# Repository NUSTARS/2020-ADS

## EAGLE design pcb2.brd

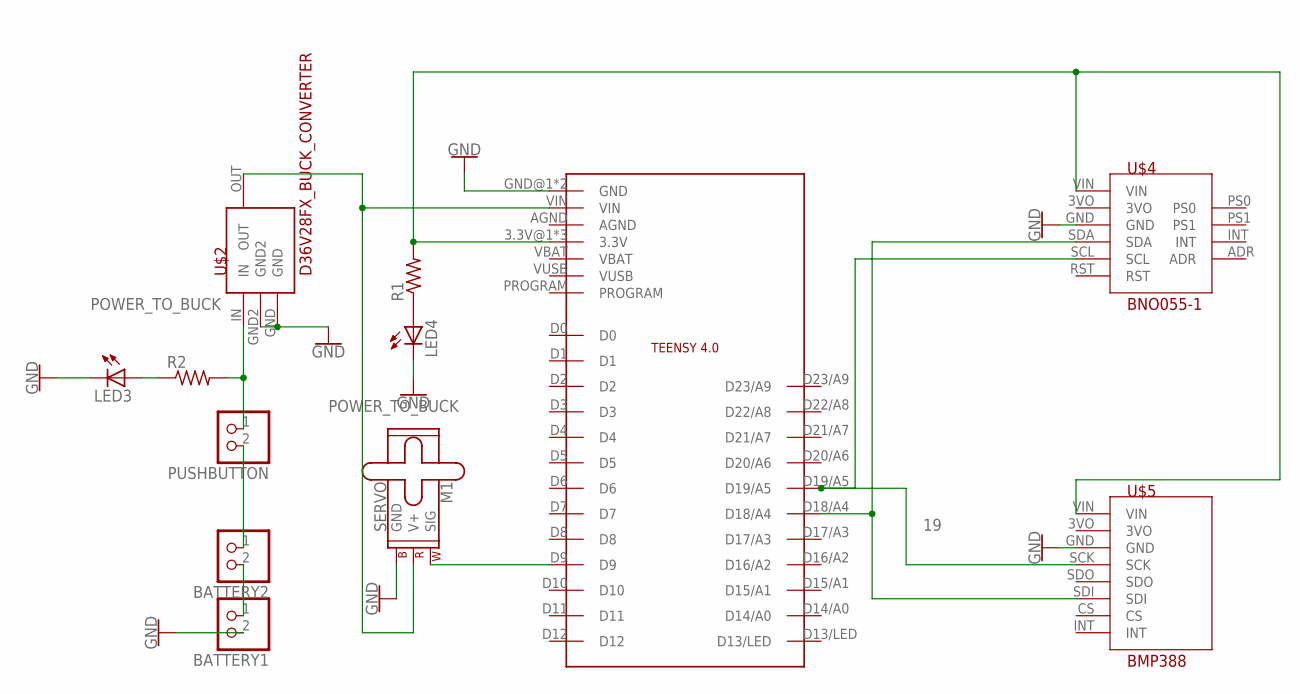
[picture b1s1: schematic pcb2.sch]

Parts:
BATTERY1, BATTERY2: JST_2PIN-THM; JST-PH-2-THM
LED3, LED4: LED5MM
M1: SERVO; 1X03
PUSHBUTTON: JST_2PIN-THM-RA; JST-PH-2-THM-RA
R1, R2: R-US_0207/12; 0207/12
U$1: TEENSY4.0
U$2: D36V28FX_BUCK_CONVERTER
U$4: BNO055-1; BNO055
U$5: BMP388

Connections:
19: U$1.D19/A5, U$4.SCL, U$5.SCK
GND: BATTERY1.2 (1), LED3.K (C), LED4.K (C), M1.3 (GND), U$1.GND@1 (GND), U$1.GND@2 (GND), U$2.GND, U$2.GND2, U$4.GND, U$5.GND
unnamed: M1.1 (SIG), U$1.D9
unnamed: U$1.D18/A4, U$4.SDA, U$5.SDI
unnamed: LED3.A, R2.1
unnamed: R1.2, U$1.3.3V@1 (3.3V), U$1.3.3V@2 (3.3V), U$1.ON/OFF (3.3V), U$4.VIN, U$5.VIN
unnamed: BATTERY2.1 (2), PUSHBUTTON.2 (1)
unnamed: LED4.A, R1.1
unnamed: BATTERY1.1 (2), BATTERY2.2 (1)
OUT: M1.2 (V+), U$1.VIN, U$2.OUT
POWER_TO_BUCK: PUSHBUTTON.1 (2), R2.2, U$2.IN

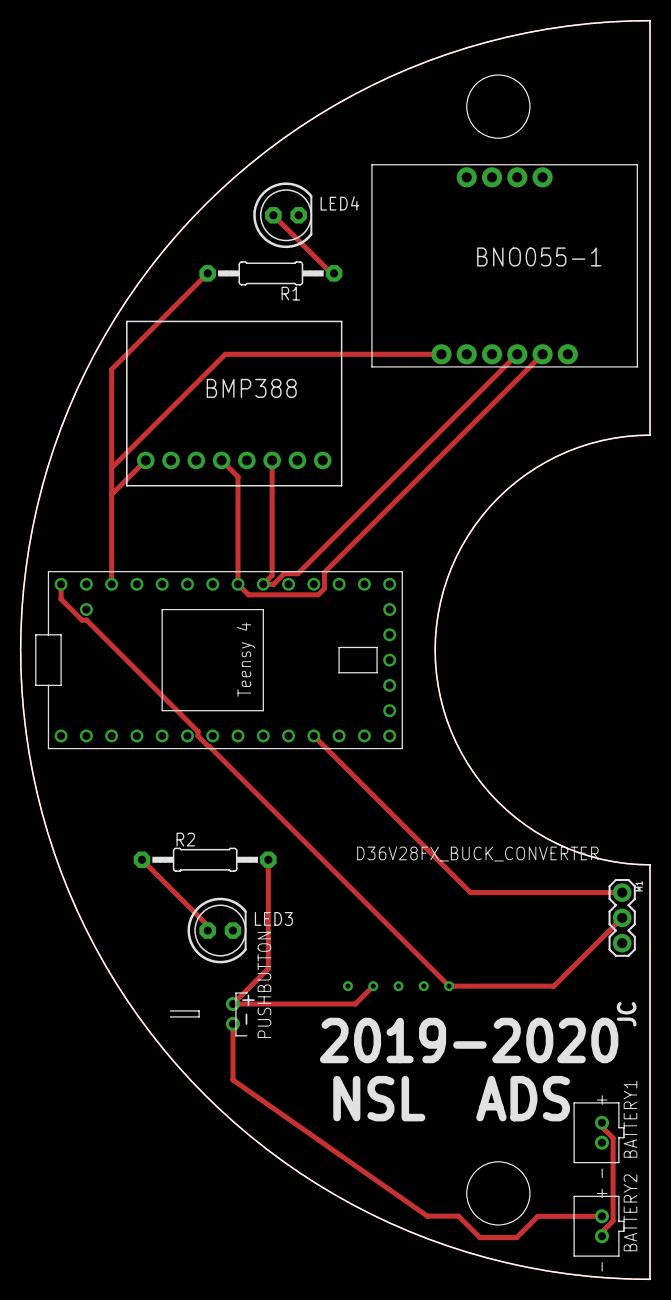
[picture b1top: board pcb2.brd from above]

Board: 2 copper layers, 63.2 x 126.5 mm, 12 parts (0 on the bottom side), 11 nets.

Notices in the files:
parts and their libraries:
SparkFun-Electromechanical: Licensing: Creative Commons ShareAlike 4.0 International - https://creativecommons.org/licenses/by-sa/4.0
